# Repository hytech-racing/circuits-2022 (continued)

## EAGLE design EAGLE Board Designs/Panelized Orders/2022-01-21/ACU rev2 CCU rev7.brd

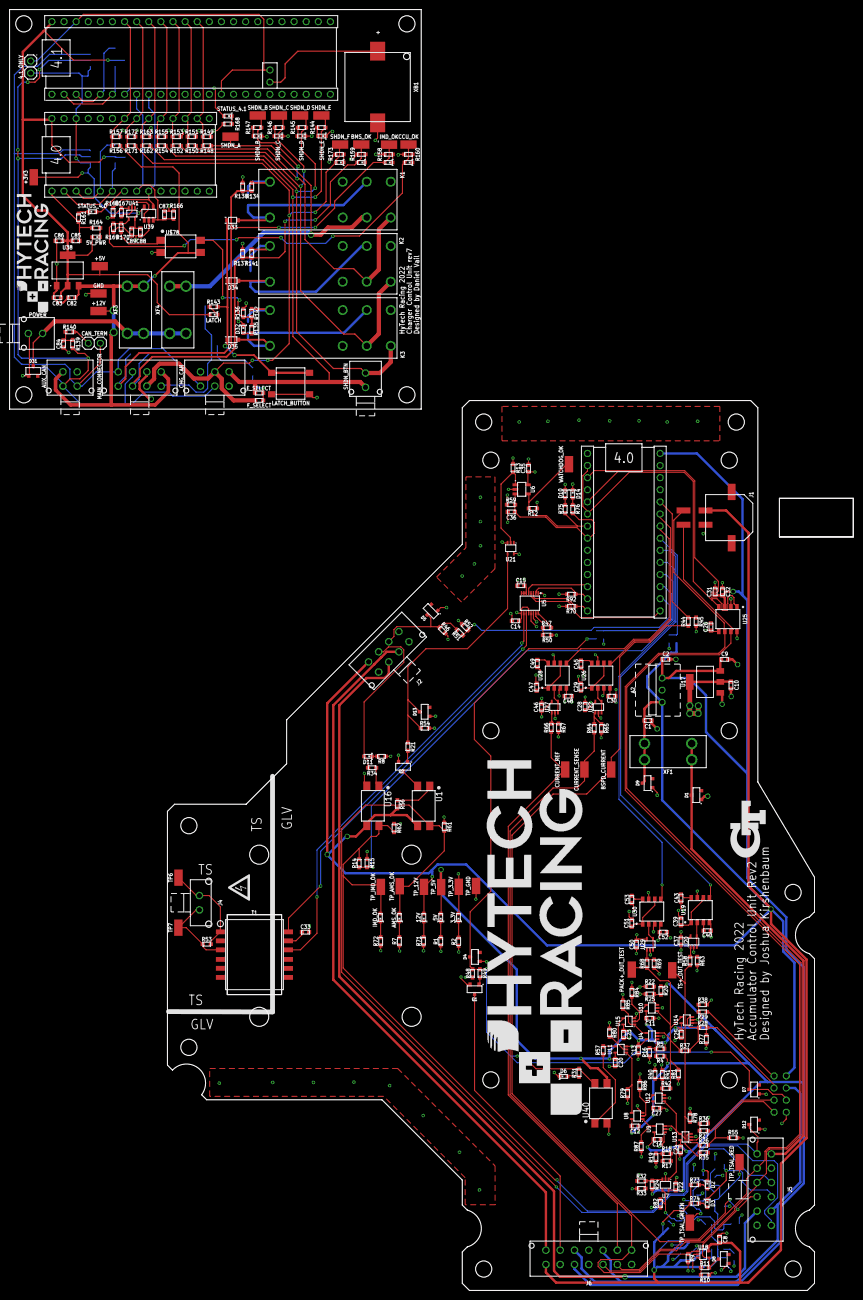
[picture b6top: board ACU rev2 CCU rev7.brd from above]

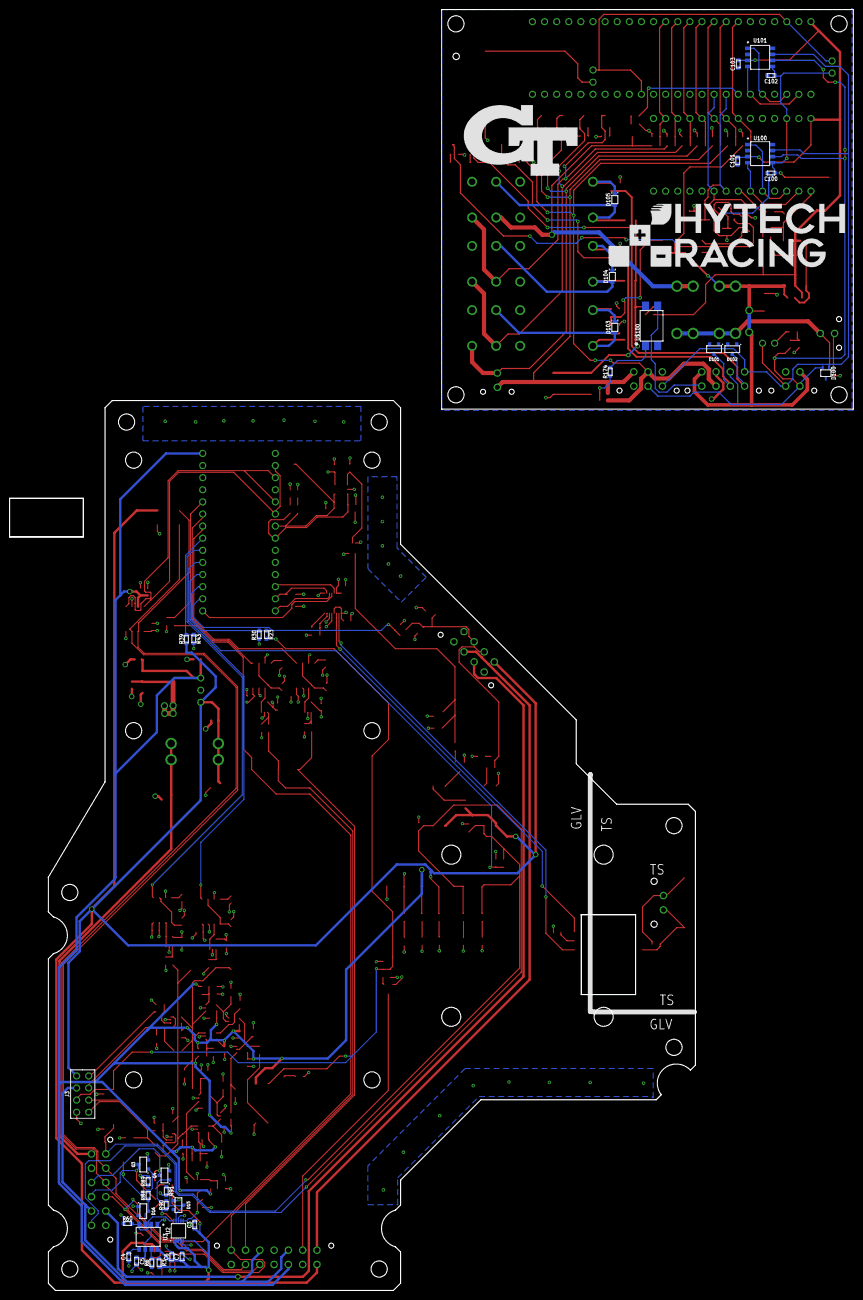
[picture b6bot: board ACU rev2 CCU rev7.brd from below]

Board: 2 copper layers, 177.0 x 268.7 mm, 357 parts (39 on the bottom side), 173 nets.

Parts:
3.3V: LED_0603_GREEN; 0603-LED
4.1_ONLY: JUMPER__1X02; 1X02
5V, 5V_PWR: LED_0603_BLUE; 0603-LED
12V: LED_0603_RED; 0603-LED
A1, A3: TEENSY_4.0; TEENSY_SHORT
A2: VOLTAGE_REGULATOR_MODULE_OKI-78SR_5V; OKI-78SR
A4: TEENSY_4.1; TEENSY_LONG_EXT
AMS_OK: LED_0603_GREEN; 0603-LED
AUX_CAN: CONNECTOR-CAN_MF_T_V_; MOLEX_MICROFIT_PTH_VERTICAL_04_DUAL
BMS_OK: LED_0603_GREEN; 0603-LED
BSPD_CURRENT: TEST_POINT; MICRO_MINIATURE
C1, C2, C82, C83: CAPACITOR_0603_25V_10UF; 0603-CAP
C3, C6: CAPACITOR_0603_25V_1UF; 0603-CAP
C4, C15, C33: CAPACITOR_0603_10V_10NF; 0603-CAP
C5, C10: CAPACITOR_0603_10V_4.7UF; 0603-CAP
C7, C8, C28, C37, C46, C50: CAPACITOR_0603_25V_0.1UF; 0603-CAP
C9, C32, C85: CAPACITOR_0603_10V_1UF; 0603-CAP
C11, C12, C13, C14, C16, C20, C22, C23, C24, C25, C26, C27, C29, C30, C31, C35, C36, C39, C40, C47, C48, C51, C52, C86, C87, C88, C89, C100, C101, C102, C103: CAPACITOR_0603_10V_0.1UF; 0603-CAP
C43, C45, C49, C53: CAPACITOR_0603_10V_680PF; 0603-CAP
C84: CAPACITOR_0603_10V_4.7NF; 0603-CAP
CAN_TERM: JUMPER__1X02; 1X02
CCU_OK: LED_0603_GREEN; 0603-LED
CHG_CAN: CONNECTOR-6_MF_T_V_; MOLEX_MICROFIT_PTH_VERTICAL_06_DUAL
CURRENT_REF: TEST_POINT; MICRO_MINIATURE
CURRENT_SENSE: TEST_POINT; MICRO_MINIATURE
D1, D5, D7, D8, D9, D12, D15, D16, D31, D101, D102: TVS_15V; SOT-23
D2, D10: LED_0603_GREEN; 0603-LED
D3, D6, D14, D32: LED_0603_RED; 0603-LED
D4, D13: TVS_8V; SOT-23
D11: LED_0603_YELLOW; 0603-LED
D33, D34, D35, D103, D104, D105: SCHOTTKY_SOD323_30V; SOD-323
D100: TVS_BIDIRECTIONAL_DUAL; SC-70-3
E_SELECT: JUMPER_0603_; 0603-RES
F_SELECT: JUMPER_0603_; 0603-RES
IMD_OK: LED_0603_ORANGE; 0603-LED
J1: CONNECTOR-CAN_μF_S_RA_; MOLEX_MICROFIT_SMD_RIGHTANGLE_04_DUAL
J2: CONNECTOR-8_MF_T_V_; MOLEX_MICROFIT_PTH_VERTICAL_08_DUAL
J3: CONNECTOR-8_S_S; FLEX_STACK_PTH_08_DUAL
J4: CONNECTOR-2_MF_T_V_; MOLEX_MICROFIT_PTH_VERTICAL_02_SINGLE
J5: CONNECTOR-12_MF_T_V_; MOLEX_MICROFIT_PTH_VERTICAL_12_DUAL
J6: CONNECTOR-14_MF_T_V_; MOLEX_MICROFIT_PTH_VERTICAL_14_DUAL
K1, K2, K3: RELAY_DPDT; RT*2*
LATCH: LED_0603_WHITE; 0603-LED
LATCH_BUTTON: BUTTON; B3S-100X
MAIN_CONNECTOR: CONNECTOR-8_MF_T_V_; MOLEX_MICROFIT_PTH_VERTICAL_08_DUAL
OKHS: LED_0603_YELLOW; 0603-LED
PACK+_OUT_TEST: TEST_POINT; MICRO_MINIATURE
POWER: CONNECTOR-2_μF_T_V_; MOLEX_MICROFIT_PTH_VERTICAL_02_DUAL
Q1, Q2, Q3, Q4: TRANSISTOR_N_MOS__PMV15ENEA; SOT-23
R1, R2, R3, R7, R8, R10, R31, R47, R50, R71, R135, R143, R144, R145, R146, R147, R158, R159, R160, R161, R164, R168, R173: RESISTOR_0603_1K; 0603-RES
R4, R18, R22, R32, R40: RESISTOR_0603_DNP; 0603-RES
R5, R17: RESISTOR_0603_4.12K; 0603-RES
R6: RESISTOR_0603_43K; 0603-RES
R9, R12, R48, R54, R55, R58, R59, R60, R61, R62, R64, R66, R68, R77, R78, R79, R80, R81, R82, R84, R85, R86, R87, R89, R91, R136, R137, R138, R165, R166, R169: RESISTOR_0603_10K; 0603-RES
R11: RESISTOR_0603_1.4K; 0603-RES
R13, R167: RESISTOR_0603_100K; 0603-RES
R14, R30, R39, R44, R51, R148, R150, R152, R154, R156, R162, R171: RESISTOR_0603_33K; 0603-RES
R15, R43, R45, R63, R65, R67, R69, R149, R151, R153, R155, R157, R163, R172: RESISTOR_0603_12K; 0603-RES
R16, R19: RESISTOR_0603_10.2K; 0603-RES
R20, R25, R26, R27, R28, R29, R33: RESISTOR_0603_11.5K; 0603-RES
R21, R49, R88, R90: RESISTOR_0603_10; 0603-RES
R23: RESISTOR_0603_18.7K; 0603-RES
R24: RESISTOR_0603_84.5K; 0603-RES
R34, R56, R70, R72, R73, R74, R92: RESISTOR_0603_2K; 0603-RES
R35, R36, R37, R38: RESISTOR_0603_10.5K; 0603-RES
R41: RESISTOR_0603_215K; 0603-RES
R42: RESISTOR_0603_11.3K; 0603-RES
R46: RESISTOR_0603_2.2K; 0603-RES
R52: RESISTOR_0603_15K; 0603-RES
R53: RESISTOR_0603_100; 0603-RES
R57, R75, R76: RESISTOR_0603_470; 0603-RES
R134, R141, R142: RESISTOR_0603_22; 0603-RES
R139, R140: RESISTOR_0603_60.4; 0603-RES
R170, R174: RESISTOR_0603_240; 0603-RES
SHDN_B: LED_0603_ORANGE; 0603-LED
SHDN_BTN: CONNECTOR-2_μF_T_V_; MOLEX_MICROFIT_PTH_VERTICAL_02_DUAL
SHDN_C: LED_0603_ORANGE; 0603-LED
SHDN_D: LED_0603_ORANGE; 0603-LED
SHDN_E: LED_0603_ORANGE; 0603-LED
SHDN_F: LED_0603_ORANGE; 0603-LED
STATUS_4.0, STATUS_4.1: LED_0603_RED; 0603-LED
T1: TRANSFORMER_HM2112ZNLT_AIRGAP; HM2112ZNLT_AIRGAP
TP6, TP7: TEST_POINT; MICRO_MINIATURE
TP22, TP23, TP24, TP25, TP26, TP27, TP28, TP29, TP30, TP31, TP32, TP33, TP34: TEST_POINT; 5015
TP_3.3V, TP_5V, TP_12V: TEST_POINT; MICRO_MINIATURE
TP_AMS_OK: TEST_POINT; MICRO_MINIATURE
TP_GND: TEST_POINT; MICRO_MINIATURE
TP_IMD_OK: TEST_POINT; MICRO_MINIATURE
TP_TSAL_GREEN: TEST_POINT; MICRO_MINIATURE
TP_TSAL_RED: TEST_POINT; MICRO_MINIATURE
TS+_OUT_TEST: TEST_POINT; MICRO_MINIATURE
U1, U16, U40: RELAY_SOLIDSTATE_NO; DIP-4
U2: ADG1423; MSOP-10
U3: LM555; SOIC-08(NARROW,0.15")
U4, U7, U9, U10, U12, U13, U14, U18, U20, U22, U27, U29: OPAMP_1_CHANNEL_OPA991; SC-70-5
U5: LTC6820; MSOP-16
U6, U39: ADM8316WBX30; SOT-23-5
U8, U11, U15: LOGICGATE_AND_DCK3; SC-70-5
U17: VOLTAGE_REGULATOR_SOT223_3.3V; SOT223
U19, U26, U28, U30: MAX7404; SOIC-08(NARROW,0.15")
U21, U41: LOGICGATE_BUFFER; SC-70-5
U25: TCAN1051HQV-Q1; SOIC-08(NARROW,0.15")
U38: VOLTAGE_REGULATOR_SOT-223_5V; SOT-223
U100, U101: MCP2562FD; SOIC-08(NARROW,0.15")
U$1, U$5: GLV
U$3, U$9, U$10: TS
U$4: HV_0.50"
U$6, U$7, U$8, U$11, U$12, U$13, U$14, U$17, U$18, U$19, U$20, U$21, U$22, U$40, U$42, U$49, U$50: MOUNTING_M3
U$15: LOGO_HYTECH_EXTRA_LARGE
U$16: LOGO_GT_0.50"
U$51: LOGO_HYTECH_MEDIUM
U$78, U$100: RELAY_SOLIDSTATE_NO; DIP-4
U$79: LOGO_HYTECH_LARGE
U$80: LOGO_GT_LARGE
WATCHDOG_OK: TEST_POINT; MICRO_MINIATURE
XB1: BATTERY_HOLDER_KEYSTONE_498; 498
XF1, XF3, XF4: FUSE_HOLDER_MINIBLADEPTH; 3568

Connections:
0.95X_DIV: R40.2, R41.2, R42.1, U12.3
0.5989V_DIV: R24.1, R32.2, R33.2, U7.3
2.5_DIV: R20.1, R22.2, R25.2, U10.3
3.56V_DIV_A: R17.1, R18.1, R19.2, U9.1
3.56V_DIV_B: R4.1, R5.1, R16.2, U4.1
4.0_CRX: A3.D0, A3.D4, U100.4
4.0_CTX: A3.D1, A3.D3, U100.1
4.1_CRX: A4.D0, A4.D4, U101.4
4.1_CTX: A4.D1, A4.D3, U101.1
12VIN: D1.3, J5.1, XF1.1, XF1.2
12V_READ: A3.D20, A4.D20, R156.2, R157.1
12V_SCALED_3.3V: A1.D19, R39.2, R43.1
60V_THRESHOLD: R82.2, U2.6, U2.7, U7.4
+3V1: 4.1_ONLY.2, A3.3.3V, C88.2, C89.2, C100.2, C102.2, TP33.1, U39.5, U41.5, U100.5, U101.5
+3V3: 3.3V.2, A1.3.3V, C10.1, C14.1, C15.2, C26.2, C28.1, C30.1, C35.1, C37.1, C40.1, C46.1, C48.1, C50.1, C52.1, R70.2, R92.2, TP_3.3V.1, U5.1, U5.6, U5.7, U5.8, U5.9, U5.12, U6.5, U17.2, U17.4, U19.4, U19.7, U20.5, U21.5, U22.5, U25.5, U26.4, U26.7, U27.5, U28.4, U28.7, U29.5, U30.4, U30.7
+5V: 5V.2, A1.VIN, A2.3, C2.1, C9.1, C11.1, C12.1, C13.1, C16.1, C20.1, C22.1, C23.1, C24.1, C25.1, C27.1, C31.2, C32.2, J6.5, R4.2, R5.2, R17.2, R18.2, R20.2, R24.2, TP_5V.1, U4.5, U7.5, U8.5, U9.5, U10.5, U11.5, U12.5, U13.5, U14.5, U15.5, U17.3, U25.3, U40.4
+5V2: 5V_PWR.2, A3.VIN, A4.VIN, C83.1, C85.1, C86.2, C101.2, C103.2, LATCH.2, TP28.1, U38.2, U38.4, U100.3, U101.3
+12V: 12V.2, A2.1, C1.1, C3.1, C6.1, C7.1, C8.1, D9.3, J1.1, J2.1, J3.5, J6.7, R3.2, R39.1, R56.2, R73.1, R74.1, TP_12V.1, U1.4, U2.1, U2.2, U2.5, U3.8, U16.4, U18.5, XF1.3, XF1.4
+12V2: AUX_CAN.1, C82.1, MAIN_CONNECTOR.4, R156.1, TP29.1, U38.3, U$78.4, XF3.3, XF3.4
ACCUMULATOR_GND: J2.7, J6.14
AIR2-: J6.13, Q1.3
AMS_OK: AMS_OK.2, J5.6, R61.2, TP_AMS_OK.1, U1.3
AMS_OK_3.3V: D13.3, R21.1, R54.1, U21.4
BMS_OK: BMS_OK.2, D101.3, MAIN_CONNECTOR.6, R137.2, R141.2, TP26.1
BSPD_CURRENT: BSPD_CURRENT.1, D8.3, J5.10, R11.2, R44.1, U18.4
BSPD_CURRENT_TEENSY: A1.D22, R44.2, R45.1
CANH: J1.4, J5.9, J6.3, U25.7
CANH1: AUX_CAN.4, CAN_TERM.2, CHG_CAN.4, D100.1, MAIN_CONNECTOR.1, U100.7, U101.7
CANL: J1.3, J5.8, J6.2, U25.6
CANL1: AUX_CAN.3, CHG_CAN.5, D100.2, MAIN_CONNECTOR.2, R139.1, U100.6, U101.6
CCU_OK: CCU_OK.2, R169.2, R170.2, TP24.1, U41.4
CHASSIS_GND: J2.6, J5.11
CS_LTC_6820: A1.D10, U5.5
CURRENT: CURRENT_SENSE.1, J6.8, R9.2, R64.1, U18.1
CURRENT_BUFFER: U22.3, U22.4, U26.2
CURRENT_FILTERED: A1.D21, U26.5
CURRENT_REF: CURRENT_REF.1, J6.9, R66.1
CURRENT_REF_BUFFER: U27.3, U27.4, U28.2
CURRENT_REF_FILTERED: A1.D20, U28.5
GND: A1.AGND/GND, A1.GND, A2.2, C1.2, C2.2, C3.2, C4.2, C5.2, C6.2, C7.2, C8.2, C9.2, C10.2, C11.2, C12.2, C13.2, C14.2, C15.1, C16.2, C20.2, C22.2, C23.2, C24.2, C25.2, C26.1, C27.2, C28.2, C29.2, C30.2, C31.1, C32.1, C33.2, C35.2, C36.2, C37.2, C39.2, C40.2, C43.2, C45.2, C46.2, C47.2, C48.2, C49.2, C50.2, C51.2, C52.2, C53.2, D1.1, D4.1, D5.1, D6.1, D7.1, D8.1, D9.1, D10.1, D12.1, D13.1, D14.1, D15.1, D16.1, J1.2, J2.4, J3.8, J5.2, J6.4, J6.6, J6.11, Q1.2, Q2.2, Q3.2, Q4.2, R1.1, R2.1, R7.1, R8.1, R9.1, R10.1, R12.1, R13.1, R15.2, R16.1, R19.1, R22.1, R25.1, R30.2, R32.1, R33.1, R36.2, R38.2, R40.1, R41.1, R43.2, R45.2, R46.1, R48.2, R50.2, R52.2, R54.2, R55.1, R59.1, R60.1, R61.1, R62.1, R63.2, R65.2, R67.2, R69.2, R71.1, R72.1, R77.1, R78.1, R79.1, R80.1, R81.1, R82.1, R84.1, R85.1, R86.1, R87.1, R89.2, R91.2, TP_GND.1, U2.4, U2.8, U3.1, U4.2, U5.13, U5.14, U6.2, U7.2, U8.3, U9.2, U10.2, U11.3, U12.2, U13.2, U14.2, U15.3, U16.2, U17.1, U18.2, U19.3, U20.2, U21.3, U22.2, U25.2, U25.8, U26.3, U27.2, U28.3, U29.2, U30.3, U40.2
GND2: A3.AGND/GND, A3.GND, A4.AGND/GND, A4.GND, A4.GND@2, AUX_CAN.2, C82.2, C83.2, C84.2, C85.2, C86.1, C87.1, C88.1, C89.1, C100.1, C101.1, C102.1, C103.1, CHG_CAN.6, D31.1, D32.1, D100.3, D101.1, D102.1, K1.14, K2.14, K3.14, LATCH_BUTTON.3, LATCH_BUTTON.4, MAIN_CONNECTOR.3, POWER.2, R136.1, R137.1, R138.1, R149.2, R151.2, R153.2, R155.2, R157.2, R158.2, R159.2, R160.2, R161.2, R163.2, R164.2, R165.2, R166.1, R167.2, R168.2, R169.1, R172.2, R173.2, SHDN_B.1, SHDN_C.1, SHDN_D.1, SHDN_E.1, TP27.1, U38.1, U39.2, U41.3, U100.2, U100.8, U101.2, U101.8, U$78.2, U$100.2, U$100.3, XB1.2
HV+_OUT_OK: R79.2, U8.4, U11.1
IM: T1.10, U5.10
IMD_OK: D12.3, IMD_OK.2, J5.7, R14.1, R62.2, TP_IMD_OK.1, U16.3
IMD_OK1: D102.3, MAIN_CONNECTOR.5, OKHS.2, R134.2, R138.2, TP25.1
IMD_OK_TEENSY: A1.D16, R14.2, R15.1
IP: T1.12, U5.11
ISO_PACK+: J3.1, R29.1
ISO_PACK-: J3.2, R28.1, R77.2
ISO_TS+: J3.3, R27.1
ISO_TS-: J3.4, R26.1, R55.2
LATCH_BUTTON: D33.C, D34.C, D35.C, LATCH_BUTTON.1, LATCH_BUTTON.2, R143.2
MHS: D5.3, J2.3, R46.2, R51.1
MHS_TEENSY: A1.D14, R51.2, R52.1
unnamed: 3.3V.1, R2.2
unnamed: 5V.1, R1.2
unnamed: C5.1, R6.1, U3.2, U3.6
unnamed: D6.2, R31.1
unnamed: C4.1, U3.5
unnamed: R3.1, R6.2, U3.7
unnamed: Q1.1, R49.2
unnamed: R34.2, U16.1
unnamed: D11.1, R8.2
unnamed: R27.2, R36.1, U13.1
unnamed: R26.2, R35.1, U13.3
unnamed: R10.2, R11.1, U18.3
unnamed: A1.D11, R92.1, U5.2
unnamed: 12V.1, R71.2
unnamed: R13.2, U6.1, U21.2
unnamed: R56.1, U1.1
unnamed: AMS_OK.1, R7.2
unnamed: D15.3, R90.1, R91.1, TP_TSAL_GREEN.1, U2.9
unnamed: D16.3, R88.1, R89.1, TP_TSAL_RED.1, U3.3
unnamed: Q2.3, U1.2
unnamed: R29.2, R38.1, U14.1
unnamed: R28.2, R37.1, U14.3
unnamed: D2.2, R73.2
unnamed: A1.D0, A1.D4, U25.4
unnamed: C39.1, U19.1, U19.6
unnamed: IMD_OK.1, R72.2
unnamed: A1.D1, A1.D3, U25.1
unnamed: Q2.1, R21.2
unnamed: R47.1, U5.16
unnamed: R47.2, R50.1, U5.15
unnamed: C33.1, T1.11
unnamed: R57.1, U11.4
unnamed: A1.D12, R70.1, U5.3
unnamed: A1.D13, U5.4
unnamed: C43.1, U19.8
unnamed: D3.2, R74.2
unnamed: D10.2, R75.1
unnamed: R58.2, R63.1, U20.1
unnamed: R57.2, U40.1
unnamed: C29.1, U26.1, U26.6
unnamed: C45.1, U26.8
unnamed: R64.2, R65.1, U22.1
unnamed: C47.1, U28.1, U28.6
unnamed: C49.1, U28.8
unnamed: R66.2, R67.1, U27.1
unnamed: C51.1, U30.1, U30.6
unnamed: C53.1, U30.8
unnamed: R68.2, R69.1, U29.1
unnamed: D14.2, R76.1
unnamed: Q3.1, R88.2
unnamed: Q4.1, R90.2
unnamed: D31.3, POWER.1, XF3.1, XF3.2, XF4.1, XF4.2
unnamed: A4.VBAT, XB1.1
unnamed: C84.1, R139.2, R140.1
unnamed: D33.A, D105.A, K1.11, K1.A2
unnamed: D34.A, D104.A, K2.11, K2.A2
unnamed: D105.C, K1.A1, R134.1
unnamed: D104.C, K2.A1, R141.1
unnamed: D103.C, K3.A1, R142.1
unnamed: R135.1, R136.2, R142.2, U$78.3
unnamed: D35.A, D103.A, K3.11, K3.A2
unnamed: D32.2, R135.2
unnamed: LATCH.1, R143.1
unnamed: R144.2, SHDN_E.2
unnamed: R145.2, SHDN_D.2
unnamed: R146.2, SHDN_C.2
unnamed: R147.2, SHDN_B.2
unnamed: OKHS.1, R158.1
unnamed: BMS_OK.1, R159.1
unnamed: CCU_OK.1, R160.1
unnamed: R161.1, STATUS_4.0.1
unnamed: 5V_PWR.1, R164.1
unnamed: 4.1_ONLY.1, A4.3V3, A4.3V3@2, A4.3V3@3
unnamed: R168.1, STATUS_4.1.1
unnamed: R170.1, U$78.1
unnamed: R167.1, U39.1, U41.2
unnamed: R173.1, SHDN_F.1
unnamed: CAN_TERM.1, R140.2
unnamed: E_SELECT.2, F_SELECT.2, R174.1
unnamed: R174.2, U$100.1
OKHS: D11.2, J2.2, R34.1
PACK+_BUFFER: U29.3, U29.4, U30.2
PACK+_FILTERED: A1.D17, U30.5
PACK+_OUT: PACK+_OUT_TEST.1, R37.2, R42.2, R68.1, R81.2, U4.3, U10.1, U14.4
PRECHARGE+_OUT_OK: R80.2, U11.2, U15.4
PRECHARGE_OK: D4.3, D7.3, J3.7, R23.1, R31.2, R48.1, R49.1, U40.3
PRECHARGE_OK_TEENSY: A1.D15, R23.2, R30.1
PRECHARGE_REACHED: R86.2, U8.2, U12.4
RPC_SWITCH: MAIN_CONNECTOR.8, U$100.4
SHDN: J3.6, J5.5, J6.10, J6.12
SHDN_A: K1.21, R148.1, TP30.1, XF4.3, XF4.4
SHDN_A_READ: A3.D14, A4.D14, R148.2, R149.1
SHDN_B: K1.24, K2.21, R147.1, R150.1, TP31.1
SHDN_B_READ: A3.D15, A4.D15, R150.2, R151.1
SHDN_C: K2.24, K3.21, R146.1, R152.1, TP32.1
SHDN_C_READ: A3.D16, A4.D16, R152.2, R153.1
SHDN_D: K3.24, R145.1, R154.1, SHDN_BTN.1, TP22.1
SHDN_D_READ: A3.D17, A4.D17, R154.2, R155.1
SHDN_E: CHG_CAN.3, E_SELECT.1, R144.1, R162.1, SHDN_BTN.2, TP23.1
SHDN_E_READ: A3.D18, A4.D18, R162.2, R163.1
SHDN_F: CHG_CAN.2, F_SELECT.1, MAIN_CONNECTOR.7, R171.1, SHDN_F.2, TP34.1
SHDN_F_READ: A3.D19, A4.D19, R171.2, R172.1
STATUS_4.0: A3.D5, STATUS_4.0.2
STATUS_4.1: A4.D5, STATUS_4.1.2
SW_SHUTDOWN: A3.D6, A4.D6, C87.2, R166.2, U39.3
TD+: J4.1, R53.2, T1.1, TP6.1
TD-: J4.2, R53.1, T1.3, TP7.1
TEENSY_OK: A1.D6, C36.1, R59.2, R76.2, U6.3
TIMER_EN: R60.2, U2.10, U3.4
TS+_OUT: R35.2, R58.1, R78.2, TS+_OUT_TEST.1, U7.1, U9.3, U12.1, U13.4
TS+_OUT_BUFFER: U19.2, U20.3, U20.4
TS+_OUT_FILTERED: A1.D18, U19.5
TS+_OUT_OV_OK: R87.2, U8.1, U9.4
TSAL_GREEN: D2.1, J5.3, Q4.3
TSAL_RED: D3.1, J5.4, Q3.3
V_PACK_REF_OV_OK: R85.2, U4.4, U15.1
V_PACK_REF_UV_OK: R84.2, U10.4, U15.2
WATCHDOG_IN: A3.D7, A4.D7, R165.1, U39.4
WATCHDOG_INPUT: A1.D5, R12.2, R75.2, U6.4, WATCHDOG_OK.1
